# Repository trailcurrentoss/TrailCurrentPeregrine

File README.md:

# TrailCurrent Peregrine

Local voice assistant for the TrailCurrent platform. Wake word, speech
recognition, the language model and speech synthesis all run on the board,
with no cloud service in the loop. Peregrine is built as a ready-to-install
Ubuntu 24.04 image for either of two boards.

## Choose your board

Peregrine supports two boards. Both run the same assistant code, answer to
the same wake word, control the same TrailCurrent devices and show up on
your network as `peregrine.local`. What differs is how smart the language
model is, how much power the board draws, and what it costs.

|  | **Radxa Dragon Q6A** (budget) | **ZimaBoard 2** (premium) |
|---|---|---|
| **Pick it when** | You want the lowest cost, or you run a really small battery bank | You want the smartest answers and are willing to pay for them |
| **Price** | Lower | Slightly higher |
| **Power draw** | Lower. A phone-class Arm chip, with the model on a dedicated low-power AI accelerator (NPU) | Higher. An Intel x86 mini-PC chip, with the model on the processor cores |
| **Language model** | Llama 3.2 **1B** | Llama 3.2 **3B**, three times the size |
| **Answer speed** | About 12 tokens/s | About 10 tokens/s (measured 9.3–10.2) |
| **Conversation memory** | 1,024 tokens (about 750 words) | 8,192 tokens (about 6,000 words) |
| **Processor / RAM** | Qualcomm QCS6490 (8 Arm cores) + Hexagon NPU, 8 GB | Intel N150 (4 x86 cores), 8 GB |
| **Storage** | M.2 2230 NVMe SSD, bought separately | 32 GB eMMC built in |
| **Installing** | Build an image, flash it over USB-C in EDL mode (or put the NVMe in a USB enclosure) | Build an installer ISO, boot the board from a USB stick |
| **Updating code on a live board** | `deploy.sh` pushes `src/` in seconds | Rebuild and reinstall the image |

### Radxa Dragon Q6A: the budget option

- **Costs the least.** The cheapest way to put Peregrine in a rig.
- **Draws the least power.** The language model runs on Qualcomm's Hexagon
  NPU, an accelerator built to do this work at low power. If you have a
  really small battery bank, this is the board to choose.
- **Quick to iterate on.** `deploy.sh` pushes code changes to a running board
  in a few seconds.
- **The trade-off is intelligence.** A 1B model is fine for small talk and
  simple questions, but it is weak at reasoning, at following instructions
  and at turning loosely worded requests into device commands. Its short
  memory also means Peregrine has to trim your device list out of its
  instructions.

### ZimaBoard 2: the premium option

Buy a ZimaBoard 2: **[ZimaBoard 2 at the Zimaspace shop](https://shop.zimaspace.com/products/zimaboard2-single-board-server?sca_ref=12564611.fDJvFR9EWxuoB4a&utm_source=dave-floyd&utm_medium=affiliate&utm_campaign=zimaspace_affiliate&utm_content=Dave-Floyd&sca_source=GitHub)**
(get the 8 GB model)

> **Affiliate link.** TrailCurrent earns a small percentage if you buy
> through this link. It costs you nothing extra.

- **Noticeably smarter.** The 3B model scores far higher than the 1B on
  Meta's published tests:

  | What it measures | Q6A (1B) | ZimaBoard 2 (3B) |
  |---|---:|---:|
  | General knowledge (MMLU) | 49% | **63%** |
  | Maths word problems (GSM8K) | 44% | **78%** |
  | Doing what it is told (IFEval) | 60% | **77%** |
  | Turning requests into device commands (BFCL v2) | 26% | **67%** |

- **Eight times the conversation memory.** Peregrine can give the model your
  whole device list, and web chats run far longer before they are trimmed.
- **Easier to install.** Write a USB stick, boot from it, type `ERASE`. There
  is no EDL mode and no separate SSD to buy.
- **The trade-offs.** It costs a little more and draws more power, so size
  your battery with that in mind. Code changes ship as a rebuilt image rather
  than through `deploy.sh`. Like any small model, it still guesses at trivia
  such as distances and dates.

The full comparison, including how the port works and what was measured, is
in [zimaboard2/docs/port-summary.md](zimaboard2/docs/port-summary.md).

**On both boards,** everyday commands such as "turn on the lights" or "what
are my water levels?" are caught by built-in phrases and never reach the
language model. The model only answers everything else.

## Architecture

Entirely offline voice pipeline:

1. **Wake word** — openWakeWord (custom `hey_peregrine` model)
2. **Speech-to-text** — faster-whisper (`base.en`, INT8 on CPU)
3. **LLM** — board-specific, behind the same loopback API on port 11434:
   - **Radxa Dragon Q6A:** Llama 3.2 1B on the Hexagon NPU via Qualcomm
     Genie (`genie_server.py`, ~12 tok/s)
   - **ZimaBoard 2:** Llama 3.2 3B in llama.cpp's `llama-server` on the CPU,
     behind a Genie-compatible bridge (`zimaboard2/src/llm_bridge.py`,
     ~10 tok/s)
4. **Text-to-speech** — Piper TTS (`en_US-libritts_r-medium`)
5. **Device control** — MQTT integration with TrailCurrent (lights, relays, sensors)
6. **Web chat UI** — `https://peregrine.local/` exposes the same on-device LLM
   to any browser on the LAN. TLS terminates inside `web_chat.py` using a
   per-board self-signed certificate; port 80 redirects to 443 and also
   serves `/ca.pem` unencrypted so first-time clients can install the CA
   before completing a TLS handshake. The chat backend proxies to the LLM
   server on loopback.
7. **Voice terminal endpoint** — `POST http://peregrine.local:8081/api/voice`
   accepts a WAV upload, runs STT → intent-or-LLM → TTS on-board, and returns
   a WAV of the spoken reply. Lets a dumb remote push-to-talk device (e.g.
   the ESP32-P4) act as a mic/speaker for Peregrine
   without needing a wake word or a separate ML pipeline. Bearer-token
   gated, LAN-only, disabled by default — see
   [docs/voice-terminal.md](docs/voice-terminal.md) for setup.

All processing happens on-device. No cloud services required for the core loop.

The assistant code in `src/` is shared. Everything board-specific lives in
the board's own layer: `image_build/` and `config/` for the Q6A,
`zimaboard2/` for the ZimaBoard 2.

## Quick start: Radxa Dragon Q6A

You need an x86_64 Linux build machine, a Radxa Dragon Q6A, an M.2 2230 NVMe
SSD, a 12 V supply, an Ethernet connection and a USB speakerphone (or a USB
mic and speaker).

```bash
# 1. Get the code
git clone https://github.com/trailcurrentoss/TrailCurrentPeregrine.git
cd TrailCurrentPeregrine

# 2. Build host setup (one time)
sudo apt install -y jsonnet bdebstrap libguestfs-tools \
    qemu-user-static binfmt-support device-tree-compiler \
    gdisk parted git curl gpg pipx rsync unzip
./image_build/preflight.sh --download-cache

# 3. Build the image (~30-50 min)
sudo ./image_build/build.sh

# 4. Put board in EDL mode and flash
sudo ./image_build/flash.sh --firmware     # one-time per board
sudo ./image_build/flash.sh --os image_build/output/peregrine-q6a-v1.0.img

# 5. Boot the board (Ethernet + 12V), wait ~3 minutes
ssh trailcurrent@peregrine.local           # password: trailcurrent
# First-login wizard runs automatically and forces a password change.

# 6. Say "hey peregrine"
```

Full walkthrough → [image_build/README.md](image_build/README.md) and the eight docs in [image_build/docs/](image_build/docs/).

## Quick start: ZimaBoard 2

You need an x86_64 Linux build machine with Docker, a
[ZimaBoard 2 (8 GB)](https://shop.zimaspace.com/products/zimaboard2-single-board-server?sca_ref=12564611.fDJvFR9EWxuoB4a&utm_source=dave-floyd&utm_medium=affiliate&utm_campaign=zimaspace_affiliate&utm_content=Dave-Floyd&sca_source=GitHub)
(affiliate link: we earn a small percentage, it costs you nothing extra),
a USB stick of 8 GB or more, a monitor and keyboard for the install, an
Ethernet connection and a USB speakerphone.

```bash
# 1. Get the code
git clone https://github.com/trailcurrentoss/TrailCurrentPeregrine.git
cd TrailCurrentPeregrine

# 2. Build the installer ISO (runs in Docker; your user must be in the docker group)
./zimaboard2/image/build.sh --version 1.0

# 3. Write it to the USB stick (the whole device, e.g. /dev/sdX, not /dev/sdX1)
sudo dd if=zimaboard2/image/output/peregrine-zimaboard2-1.0.iso \
    of=/dev/sdX bs=4M conv=fsync status=progress

# 4. In the board's firmware setup: boot from USB, and set
#    "Restore on AC power loss" to Power on

# 5. Boot from the stick, accept the eMMC, type ERASE, remove the stick,
#    press Enter. The board reboots into Peregrine.

# 6. Connect Ethernet and the speakerphone
ssh trailcurrent@peregrine.local           # password: trailcurrent
# First-login wizard runs automatically and forces a password change.

# 7. Say "hey peregrine"
```

Full walkthrough, including a network install with no USB stick →
[zimaboard2/docs/install.md](zimaboard2/docs/install.md).

## Releases

Two release tracks:
- **Image release** — a full reinstall, used when the OS, Python packages, LLM, or branding change. Q6A: [image_build/docs/08-cutting-a-release.md](image_build/docs/08-cutting-a-release.md). ZimaBoard 2: build a new ISO with `./zimaboard2/image/build.sh --version X.Y`.
- **Software release** ([docs/software-releases.md](docs/software-releases.md)) — `src/`, models, and service files only, pushed to live Q6A boards via `deploy.sh`. ZimaBoard 2 boards take the same changes in their next image.

## Project structure

```
TrailCurrentPeregrine/
├── README.md                       This file
├── LICENSE
│
├── src/                            ★ Shared by both boards ★
│   ├── assistant.py                Main voice assistant loop
│   ├── genie_server.py             NPU LLM HTTP server (loopback, Q6A only)
│   ├── stt.py                      Reusable faster-whisper wrapper (used by web_chat.py)
│   ├── tts.py                      Piper TTS streaming helper
│   └── web_chat.py                 LAN-facing chat UI (443) + voice terminal endpoint (8081)
│
├── models/
│   ├── hey_peregrine.onnx          Custom wake word model (both boards)
│   └── hey_peregrine.onnx.data
│
├── scripts/
│   └── generate-certs.sh           Per-board web UI certificate (both boards)
│
├── docs/
│   ├── ZimaBoard2/README.md        ZimaBoard 2 port design
│   ├── mqtt-ca-cert.md             MQTT CA certificate install and rotation
│   ├── software-releases.md        Software-only releases (Q6A)
│   ├── voice-terminal.md           Push-to-talk /api/voice endpoint
│   └── future-vision-modes.md      Vision modes roadmap
│
├── deploy.sh                       Dev tool — push src/ to a running Q6A
│
├── config/                         Q6A systemd units (baked into the image)
│   ├── voice-assistant.service
│   ├── genie-server.service
│   └── peregrine-chat.service
│
├── image_build/                    ★ Radxa Dragon Q6A image build ★
│   ├── README.md                   Quick start
│   ├── docs/                       8 detailed walkthroughs
│   ├── build.sh                    Top-level build orchestrator
│   ├── preflight.sh                Build host setup verification
│   ├── flash.sh                    edl-ng wrapper for SPI NOR + NVMe flashing
│   ├── rsdk/                       Vendored Radxa SDK with Peregrine hooks
│   ├── firmware/                   SPI NOR firmware (committed)
│   ├── files/                      Static files baked into the image
│   ├── cache/                      NPU model + Piper voice (gitignored)
│   └── output/                     Built images (gitignored)
│
├── zimaboard2/                     ★ ZimaBoard 2 image build ★
│   ├── README.md                   Overview and layout
│   ├── docs/                       Install guide, benchmarks, port summary
│   ├── src/llm_bridge.py           Genie-compatible API in front of llama-server
│   ├── config/                     ZimaBoard systemd units, llm.env, ALSA, netplan
│   ├── tools/peregrine-model       List, switch, import and test LLMs
│   └── image/                      Installer ISO build (Docker), network installer, VM test
│
├── training/                       Wake-word training pipeline (large, mostly gitignored)
│   ├── *.py                        Recording / generation scripts
│   ├── recordings/                 Stray clips (gitignored)
│   └── openwakeword-trainer/       Training pipeline + configs
│
├── CAD/                            Enclosure
└── EDA/                            HAT PCB
```

## Install and update paths

| Board | Path | When | Time |
|---|---|---|---|
| Q6A | **Image build + flash** ([image_build/](image_build/)) | New board, OS package change, model update, dependency change | ~50 min build + ~10 min flash |
| Q6A | **`deploy.sh`** | Iterating on `src/` on an already-flashed board | ~5 sec |
| ZimaBoard 2 | **ISO build + USB install** ([zimaboard2/docs/install.md](zimaboard2/docs/install.md)) | New board, and any change at all | Build, then a few minutes to install |
| ZimaBoard 2 | **Network install** (`zimaboard2/image/netinstall.sh`) | Replacing the OS on a board you can SSH into | As above, no USB stick |

The image build is the **canonical install path** on both boards. `deploy.sh`
is a Q6A development tool, and its changes are lost on the next reflash (see
[image_build/docs/07-development.md](image_build/docs/07-development.md)). It
checks the board first and refuses to push to a ZimaBoard 2, whose units
differ from the Q6A's.

## Verifying audio on a running board

```bash
ssh trailcurrent@peregrine.local
peregrine-self-test                # audio, LLM, wake word (plus the NPU on a Q6A)

# Or by hand
aplay -l
arecord -l
speaker-test -t wav -c 2 -l 1
arecord -d 5 -f S16_LE -r 16000 /tmp/test.wav && aplay /tmp/test.wav
```

## Configuring MQTT

The first-login wizard offers MQTT setup. To change it later:

```bash
ssh trailcurrent@peregrine.local
nano ~/assistant.env
sudo systemctl restart voice-assistant

# Monitor live logs
sudo journalctl -u voice-assistant -f
```

Without MQTT configured, the assistant still answers general questions —
device-control commands will just report "not connected."

For TLS to a self-signed Headwaters broker, the CA cert is installed at
`/home/trailcurrent/ca.pem` and obtained from the **Headwaters Settings
page** (https://headwaters.local → Settings → CA Certificate panel). For
the install/rotation procedure see [docs/mqtt-ca-cert.md](docs/mqtt-ca-cert.md).

## Time sync

The clock is set on every boot by `systemd-timesyncd` (the Q6A has no RTC
battery, so it depends on this). Both images ship with
`/etc/systemd/timesyncd.conf.d/10-trailcurrent.conf` pointing at
`headwaters.local` (resolved via mDNS through libnss-mdns + avahi). If
Headwaters isn't reachable — bench/dev networks, vehicle off the LAN —
timesyncd falls back to `pool.ntp.org`. Check sync status with
`timedatectl status`.

## Voice Commands

With MQTT connected, the assistant responds to:

| Command | Example phrases |
|---|---|
| **Lights on/off** | "Turn on the lights", "Lights off", "Turn off light 3" |
| **Light brightness** | "Set lights to 50 percent", "Dim light 2 to 25 percent" |
| **Light status** | "Are the lights on?", "Which lights are on?" |
| **Named devices** | "Turn on the water pump", "Turn off the awning light" |
| **Relay status** | "What relays are on?", "Switch status" |
| **Everything** | "Turn off everything", "Turn on all the lights" |
| **Water tanks** | "What are my water levels?", "How much fresh water do I have?", "How full is the grey tank?", "Black tank status" |
| **Temperature** | "What's the temperature?", "How hot is it?" |
| **Humidity** | "What's the humidity?" |
| **Battery/energy** | "What's the battery level?", "How much solar?" |
| **Location** | "Where are we?", "What's our location?" |
| **General questions** | Anything else is answered by the LLM |

Device commands and sensor queries use fast regex-based intent matching (no LLM round-trip). Unrecognized requests fall through to the LLM.

The same intent + LLM path is exposed over HTTP at `POST /api/voice` on port 8081, letting a push-to-talk remote (e.g. the ESP32-P4) act as a mic/speaker for Peregrine without shipping any ML on the client side. See [docs/voice-terminal.md](docs/voice-terminal.md) to enable and test.

Device names are configured in the TrailCurrent web UI and synced via MQTT. Both Torrent (PWM lights) and Switchback (relays) devices are supported. Only Torrent lights support brightness — Switchback relays are on/off only. When you say "turn off all the lights", both Torrent lights and any Switchback relays configured as type "light" are turned off.

## Configuration

All settings are controlled via environment variables. On the board, site-specific config lives in `~/assistant.env` (loaded by the systemd service). This file is never overwritten by setup or deploy. A reinstall does replace it, so copy it off first.

The defaults below are the code's. Each board's `voice-assistant.service` overrides a few of them for its hardware; the ZimaBoard 2 column shows those overrides.

| Variable | Default | ZimaBoard 2 | Description |
|---|---|---|---|
| `WAKE_MODEL` | `hey_peregrine` | | openWakeWord model name |
| `WAKE_MODEL_PATH` | *(auto-detected)* | | Path to custom `.onnx` wake word model |
| `WAKE_THRESHOLD` | `0.85` | | Wake word detection threshold (0.0–1.0) |
| `WAKE_ACTIVATIONS` | `3` | | Consecutive frames above threshold required to trigger |
| `WHISPER_SIZE` | `base.en` | | Whisper model size |
| `OLLAMA_URL` | `http://localhost:11434` | | LLM API endpoint (`genie_server.py` on the Q6A, `llm_bridge.py` on the ZimaBoard 2) |
| `OLLAMA_MODEL` | `llama3.2:1b-npu` | | Model identifier for LLM requests |
| `PIPER_MODEL` | `~/piper-voices/en_US-libritts_r-medium.onnx` | | Path to Piper voice model |
| `SILENCE_THRESHOLD` | `500` | | Amplitude below which audio is silence |
| `SILENCE_DURATION` | `1.5` | | Seconds of silence before stopping recording |
| `MAX_RECORD_SECONDS` | `15` | `30` | Longest a single spoken request may run |
| `WAKE_MIN_RMS` | `300` | `0` (off) | Skip the wake-word model on chunks quieter than this. The ZimaBoard has CPU to spare, so it listens to every chunk |
| `LLM_SYSTEM_PROMPT_BUDGET_CHARS` | `2200` | `8000` | Size cap on the LLM's instructions. Sized to the model's context window |
| `PEREGRINE_LLM_GATE` | *(empty = off)* | `/run/peregrine/llm-gate.sock` | Yield gate: pauses a long web-chat answer while a voice command runs |
| `CPU_THREADS` | `8` | `3` | Threads for faster-whisper inference |
| `MQTT_BROKER` | *(empty = disabled)* | | MQTT broker hostname or IP |
| `MQTT_PORT` | `8883` | | MQTT broker port |
| `MQTT_USE_TLS` | `true` | | Enable TLS for MQTT connection |
| `MQTT_CA_CERT` | *(empty)* | | Path to CA certificate for self-signed certs |
| `MQTT_USERNAME` | *(empty)* | | MQTT authentication username |
| `MQTT_PASSWORD` | *(empty)* | | MQTT authentication password |
| `HEADWATERS_URL` | `https://<MQTT_BROKER>` | | Base URL of the Headwaters REST API |
| `HEADWATERS_API_KEY` | *(empty)* | | `rv_...` API key from Headwaters → Settings → API Keys. Required for the "where am I", "nearby cities", and "capital of the state I'm in" intents (falls back to raw lat/lon without one). |
| `INTENT_RPC_PORT` | `11435` | | Loopback port the chat UI uses to reach the intent handler |
| `PEREGRINE_VOICE_PORT` | `8081` | | LAN listener for the `/api/voice` push-to-talk endpoint |
| `PEREGRINE_VOICE_TOKEN` | *(empty = disabled)* | | Bearer token required on every `/api/voice` request. See [docs/voice-terminal.md](docs/voice-terminal.md) |
| `PEREGRINE_VOICE_MAX_BYTES` | `1048576` | | Upload body cap (~30 sec of 16 kHz mono) |
| `PEREGRINE_VOICE_TARGET_SR` | `16000` | | Sample rate of the returned WAV (match the client codec) |

## MQTT Topics

The assistant subscribes to these topics for sensor data and device config:

| Topic | Data |
|---|---|
| `local/airquality/temphumid` | `{"tempInC": °C, "tempInF": °F, "humidity": %}` |
| `local/airquality/status` | `{"tvoc_ppb": ppb, "eco2_ppm": ppm}` |
| `local/energy/status` | `{"battery_percent": %, "battery_voltage": V, "solar_watts": W}` |
| `local/gps/latlon` | `{"latitude": float, "longitude": float}` |
| `local/gps/time` | `{"year": int, "month": int, "day": int, "hour": int, "minute": int, "second": int}` (UTC) |
| `local/gps/alt` | `{"altitudeInMeters": float, "altitudeFeet": int}` |
| `local/water/status` | `{"fresh": %, "grey": %, "black": %}` (0–100 percent) |
| `local/lights/+/status` | `{"state": 0/1, "name": "..."}` (Torrent lights) |
| `local/relays/+/status` | `{"state": 0/1}` (Switchback relays) |
| `local/thermostat/status` | Thermostat state |
| `local/config/pdm_channels` | Torrent channel names/types (retained) |
| `local/config/relay_channels` | Switchback channel names/types (retained) |

For device commands, it publishes:

| Topic | Payload |
|---|---|
| `local/lights/{id}/command` | `{"state": 0/1}` (Torrent lights) |
| `local/lights/{id}/brightness` | `{"brightness": 0-255}` (Torrent lights only) |
| `local/relays/{channel}/command` | `{"state": 0/1}` (Switchback individual relay toggle) |
| `local/relays/all/command` | `{"state": 0/1}` (Switchback all relays on/off) |

## Hardware

**Radxa Dragon Q6A (budget)**

- **Board**: Radxa Dragon Q6A (Qualcomm QCS6490 SoC, 8 GB RAM)
- **NPU**: Hexagon DSP v68 (12 TOPS) — runs LLM inference at ~12 tok/s
- **Audio**: USB microphone + speaker (auto-detected via ALSA, uses arecord/aplay)
- **Storage**: M.2 2230 NVMe SSD with Radxa OS Noble 24.04 (Ubuntu-based)
- **Power**: 12 V

**ZimaBoard 2 (premium)**: [buy a ZimaBoard 2](https://shop.zimaspace.com/products/zimaboard2-single-board-server?sca_ref=12564611.fDJvFR9EWxuoB4a&utm_source=dave-floyd&utm_medium=affiliate&utm_campaign=zimaspace_affiliate&utm_content=Dave-Floyd&sca_source=GitHub)
(affiliate link: we earn a small percentage, it costs you nothing extra)

- **Board**: ZimaBoard 2, 8 GB model (Intel N150, 4 cores)
- **LLM**: llama.cpp on three CPU cores, ~10 tok/s; one core kept for the voice loop
- **Audio**: USB speakerphone (auto-detected via ALSA, uses arecord/aplay); onboard audio is disabled
- **Storage**: 32 GB internal eMMC with Ubuntu Noble 24.04 (amd64)
- **Power**: wired to the house battery; see [zimaboard2/docs/install.md](zimaboard2/docs/install.md) for the firmware power-loss setting

## Wake Word Training

The custom "Hey Peregrine" wake word model is trained using the pipeline in `training/openwakeword-trainer/`. See that directory's [README](training/openwakeword-trainer/README.md) for the full 13-step pipeline and configuration reference.

Training runs on a dev workstation with an NVIDIA GPU (not on the target board).

### Recording Real Voice Clips

Real voice clips significantly improve detection accuracy over synthetic-only training:

```bash
cd training/

# Positive clips (the wake word)
python3 record_wake_word.py --phrase "hey peregrine" --count 50

# See suggested negative phrases to reduce false positives
python3 record_wake_word.py --suggest

# Record negative clips (similar-sounding phrases the model should reject)
python3 record_wake_word.py --phrase "hey pelican" --count 10 --negative --auto
```

Aim for 200+ positive clips and 50-100 negative clips from similar-sounding phrases.

### Ambient Noise Negatives

The model also needs non-speech negatives (silence, fan noise, road noise) to avoid false triggers on ambient sounds. There are two sources: synthetic/downloaded clips, and real recordings from a microphone.

#### Synthetic + downloaded clips

```bash
cd training/

# Generate synthetic noise clips + download MS-SNSD (MIT) and MUSAN (CC0) recordings
python3 generate_ambient_negatives.py
```

This populates `real_clips_negative/` with ambient noise clips across categories (fan noise, road noise, rain, HVAC, silence, etc.).

#### Recording real ambient noise from a microphone

For best results, also capture real ambient audio from the environment where the device will be used (vehicle interior, campsite, etc.). The `record_ambient_negatives.py` script records 2-second clips in a continuous loop for a set duration.

1. Find your microphone's ALSA device:
   ```bash
   arecord -l
   ```
   Look for your USB mic (e.g. `card 2: USB [Jabra SPEAK 410 USB], device 0` → `hw:2,0`).

2. Run a recording session (from the `training/` directory):
   ```bash
   python3 record_ambient_negatives.py --device hw:2,0 --minutes 30
   ```
   This records ~720 clips over 30 minutes, saving them to `training/real_clips_negative/ambient_recorded/`. Clips that are too quiet are automatically discarded. Press Ctrl+C to stop early.

   Additional options: `--pause 1.0` (gap between clips, default 0.5s), `--min-rms 100` (minimum loudness to keep, default 50).

3. Run multiple sessions to capture different environments — clips are appended, never overwritten.

#### Build the ambient feature file

After adding clips from either source, rebuild the feature file used by training:

```bash
python3 build_ambient_features.py
```

This produces `negative_features_ambient.npy` used during training.

### Retraining the Model

After recording new clips and rebuilding features, retrain the wake word model.

**1. Prepare (from the `training/` directory):**

```bash
cd openwakeword-trainer
source ~/.oww-trainer-venv/bin/activate      # your openwakeword trainer venv
rm -f output/hey_peregrine.onnx output/hey_peregrine.onnx.data
rm -f export/hey_peregrine.onnx export/hey_peregrine.onnx.data
```

- Stop anything else that holds GPU memory (image generators, other ML jobs). On an 8 GB card, training runs out of memory if another job holds a few GB.
- Old model files must be deleted — the pipeline skips training if they exist.

**2. Run training (~16 minutes on an NVIDIA GPU):**

```bash
python train_wakeword.py --config configs/hey_peregrine.yaml --from train
```

The `onnx_tf` error at the end is harmless — the ONNX model exports successfully, it just can't convert to TFLite (which isn't used).

**3. After training completes, copy the model to the project `models/` directory:**

```bash
cp output/hey_peregrine.onnx ../../models/
cp output/hey_peregrine.onnx.data ../../models/
```

### Deploying a New Model

After training, copy the model to the board. The model-only update works on
both boards:

```bash
scp models/hey_peregrine.onnx* trailcurrent@peregrine.local:/home/trailcurrent/models/
ssh trailcurrent@peregrine.local "sudo systemctl restart voice-assistant"

# Q6A only: full deploy (code + model + service) — see image_build/docs/07-development.md
./deploy.sh peregrine.local
```

For a permanent install (so the new model survives a reinstall), leave the
new files in `models/` and rebuild the image. Both builds take the wake word
from `models/`: `sudo ./image_build/build.sh` for the Q6A,
`./zimaboard2/image/build.sh --version X.Y` for the ZimaBoard 2.

## Third-Party Licenses

### Runtime Components

| Component | License |
|---|---|
| [openWakeWord](https://github.com/dscripka/openWakeWord) | Apache 2.0 |
| [faster-whisper](https://github.com/SYSTRAN/faster-whisper) | MIT |
| [Llama 3.2 1B](https://huggingface.co/meta-llama/Llama-3.2-1B) (Q6A) | Llama 3.2 Community |
| Qualcomm Genie (genie-t2t-run) (Q6A) | Qualcomm proprietary (bundled with NPU model) |
| [Llama 3.2 3B Instruct](https://huggingface.co/meta-llama/Llama-3.2-3B-Instruct) (ZimaBoard 2) | Llama 3.2 Community |
| [llama.cpp](https://github.com/ggml-org/llama.cpp) (ZimaBoard 2) | MIT |
| [Piper TTS](https://github.com/rhasspy/piper) | MIT |
| [Piper voice: en_US-libritts_r-medium](https://huggingface.co/rhasspy/piper-voices) | CC-BY-4.0 |
| [ONNX Runtime](https://github.com/microsoft/onnxruntime) | MIT |
| [paho-mqtt](https://github.com/eclipse/paho.mqtt.python) | EPL-2.0 / EDL-1.0 |

### Wake Word Training Data

| Dataset | License |
|---|---|
| [LibriSpeech](https://www.openslr.org/12) | CC-BY-4.0 |
| [VoxPopuli](https://github.com/facebookresearch/voxpopuli) | CC0 |
| [MS-SNSD](https://github.com/microsoft/MS-SNSD) | MIT |
| [MUSAN](https://www.openslr.org/17/) | CC0 / CC-BY-3.0 |

The Piper `libritts_r` voice model is derived from [LibriTTS-R](https://www.openslr.org/141/) (CC-BY-4.0). Attribution: Koizumi et al., "LibriTTS-R: A Restored Multi-Speaker Text-to-Speech Corpus", 2023.

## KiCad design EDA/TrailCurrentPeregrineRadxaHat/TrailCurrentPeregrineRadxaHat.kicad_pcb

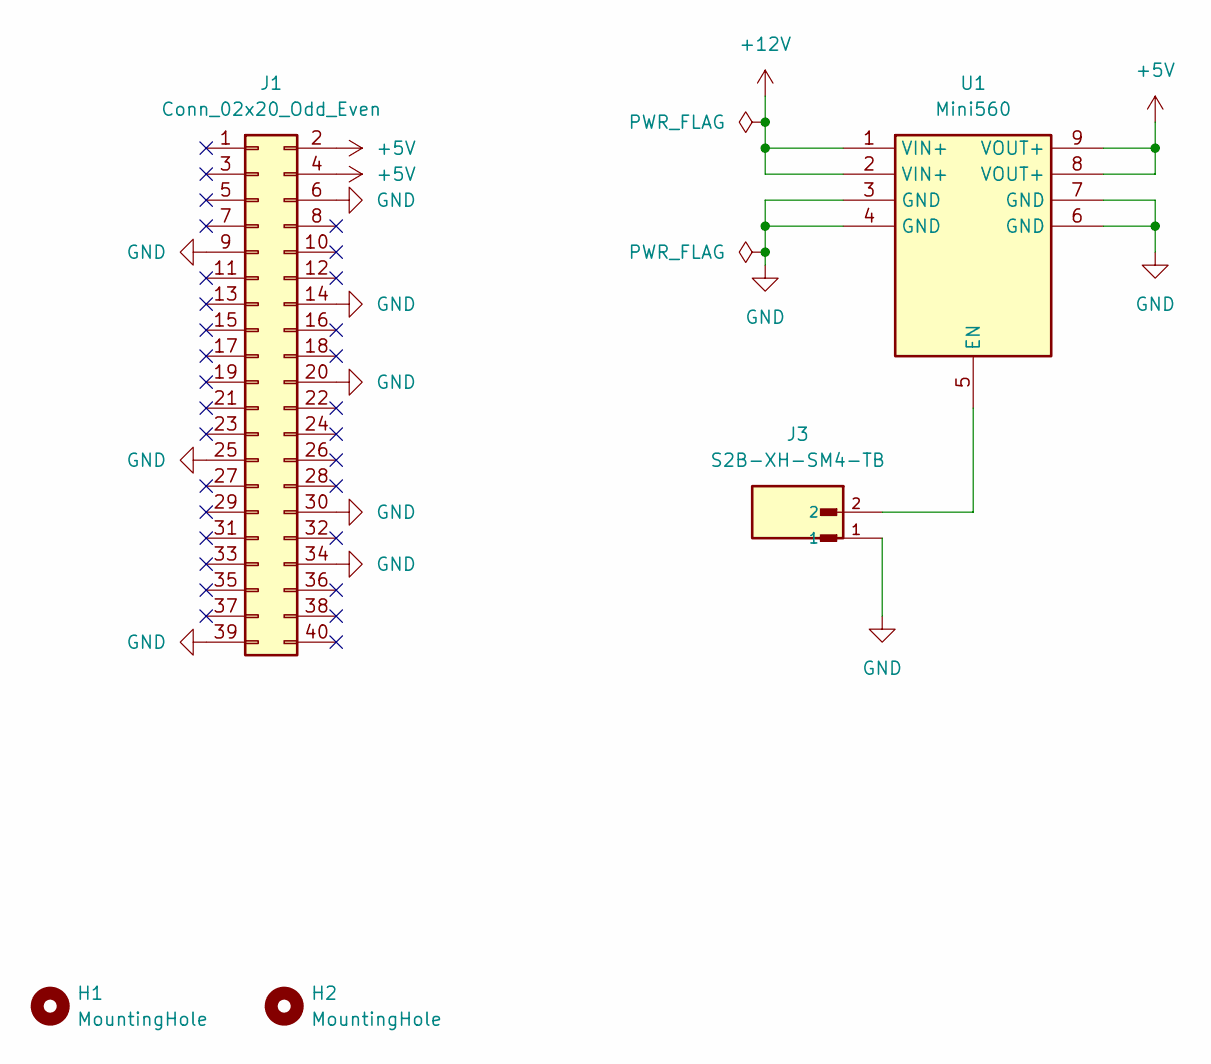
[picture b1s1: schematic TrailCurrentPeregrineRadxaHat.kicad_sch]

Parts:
H1, H2: MountingHole; MountingHole_3.5mm
J1: Conn_02x20_Odd_Even; PinHeader_2x20_P2.54mm_Vertical
J3: S2B-XH-SM4-TB; JST_S2B-XH-SM4-TB
U1: Mini560; Manufacturer_Part_Number Mini560

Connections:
+5V: J1.2, J1.4, U1.8 (VOUT+), U1.9 (VOUT+)
+12V: U1.1 (VIN+), U1.2 (VIN+)
GND: J1.6, J1.9, J1.14, J1.20, J1.25, J1.30, J1.34, J1.39, J3.1, U1.3 (GND), U1.4 (GND), U1.6 (GND), U1.7 (GND)
unnamed: J3.2, U1.5 (EN)

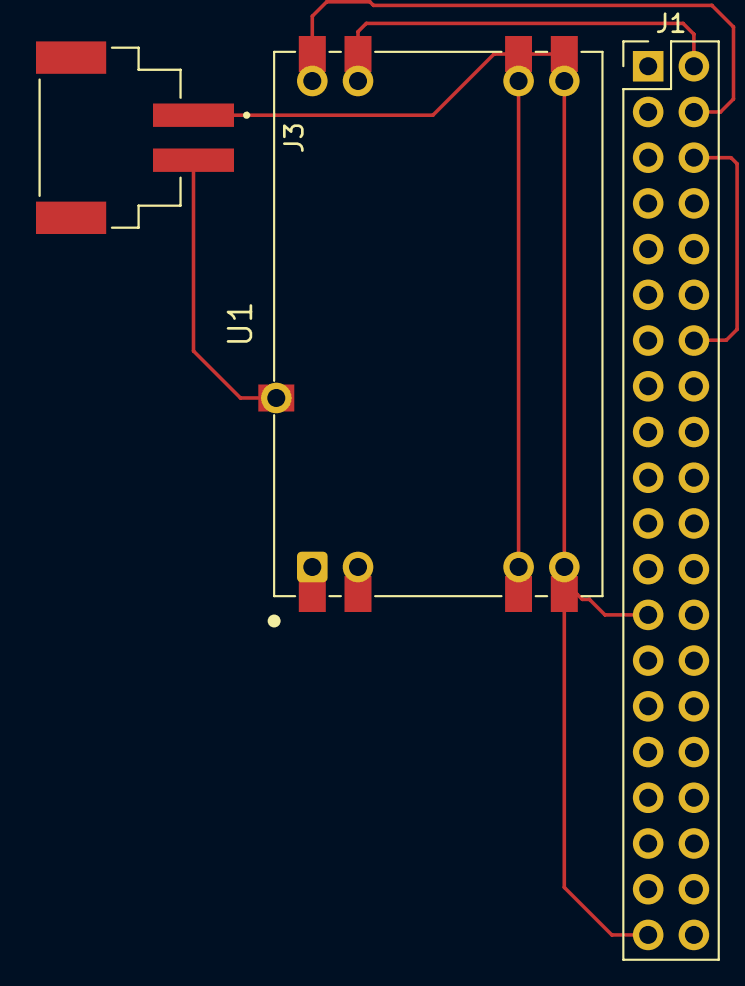
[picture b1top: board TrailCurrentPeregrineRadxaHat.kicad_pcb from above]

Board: 2 copper layers, 5 parts (0 on the bottom side), 4 nets.

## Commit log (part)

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2026-03-07 Starting project
2026-03-07 Bringing in opwnwakeword
2026-03-07 Updated documentation, fixed steps in deploy, added wakeword notes
2026-03-07 Work started on HAT and Case
2026-03-08 Adding avahi for mdns resolution to new boards
2026-03-08 Enhanced setup-board.sh with mode selection for debug and production. Added functionality to enable/disable WiFi and HDMI based on mode, improved logging, and refined package upgrade command.
2026-03-10 Updated readme to showcase the physical device
2026-03-14 Fixed optimistic state. State always needs to come from the devices themselves
2026-03-15 Adding level commands
2026-04-12 Moving to image build so that users can easily flash new Radxa boards with Peregrine image
2026-04-13 Updating default values in .env and disabling sound test in initial setup
2026-04-14 Image and initial setup are working
2026-04-21 Performance improvements
2026-04-21 Thermal fix and performance improvements
2026-05-12 Removing EDA since we are not designing a HAT for this
2026-05-12 Updating documentation and bug fixes for radio tuning
2026-05-13 Added intents to get whats playing on playbill and refined other commands too
2026-05-15 Added headwaters as NTP server to sync time
2026-05-17 Added web UI for peregrine and APIs that other clients can call
